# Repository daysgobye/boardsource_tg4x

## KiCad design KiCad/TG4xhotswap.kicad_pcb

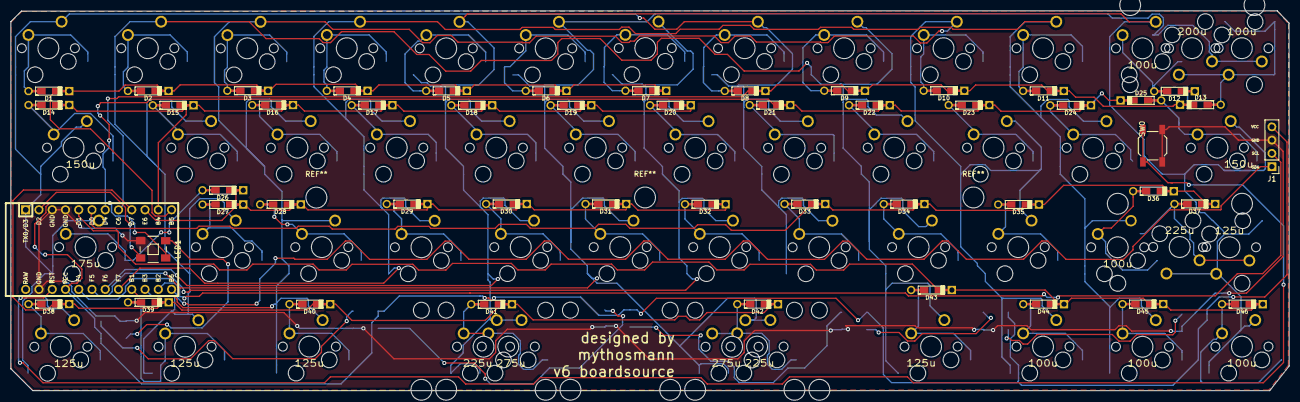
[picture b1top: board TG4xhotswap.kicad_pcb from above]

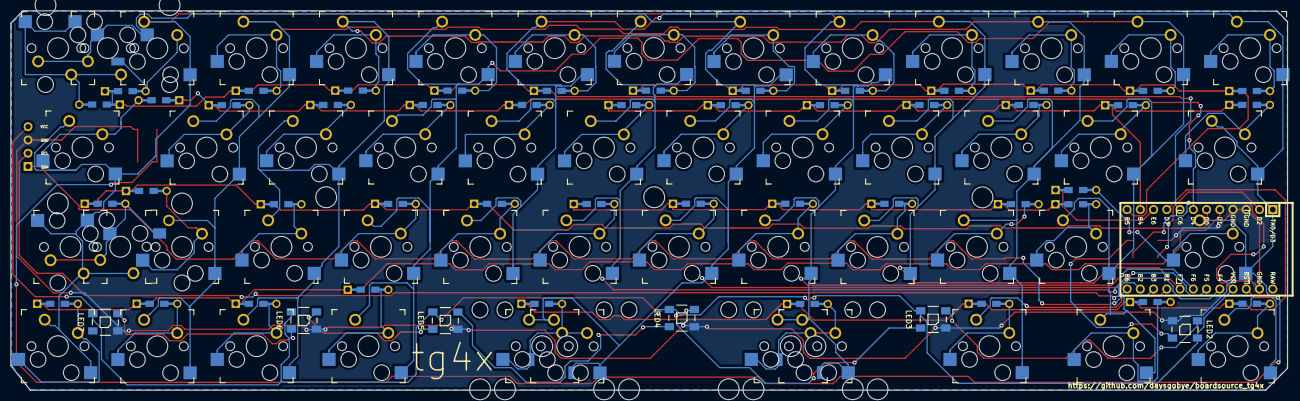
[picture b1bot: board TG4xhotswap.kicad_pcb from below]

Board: 2 copper layers, 244.8 x 72.8 mm, 106 parts (7 on the bottom side), 73 nets.

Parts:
100u, 100u#2, 100u#3, 100u#4, 100u#5, 100u#6, 125u, 125u#2, 125u#3, 125u#4, 125u#5, 150u, 150u#2, 175u, 200u, 225u, 225u#2, 225u#3, 275u, 275u#2: SW_Push; Kailh_socket_optional
D1, D2, D3, D4, D5, D6, D7, D8, D9, D10, D11, D12, D13, D14, D15, D16, D17, D18, D19, D20, D21, D22, D23, D24, D25, D26, D27, D28, D29, D30, D31, D32, D33, D34, D35, D36, D37, D38, D39, D40, D41, D42, D43, D44, D45, D46: 1N4148; Diode-dual
J1: Conn_01x04_Female; PinHeader_1x04_P2.54mm_Vertical
LED1, LED2, LED3, LED4, LED5, LED6, LED7: WS2812B
SW0: SW_Push; SW_SPST_SKQG_WithStem
SW1, SW2, SW3, SW4, SW5, SW6, SW7, SW8, SW9, SW10, SW11, SW15b1, SW16b1, SW17b1, SW18b1, SW19b1, SW20b1, SW21b1, SW22b1, SW23b1, SW24b1, SW27, SW28, SW29, SW30, SW31, SW32, SW33, SW34, SW35: SW_Push; Kailh_socket_optional
U1: ProMicro; ArduinoProMicro

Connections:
COL0: 125u.1, 150u.1, 175u.1, SW1.1, SW8.1, SW21b1.1, SW33.1, U1.1
COL1: 125u#2.1, 125u#5.1, SW2.1, SW9.1, SW15b1.1, SW22b1.1, SW27.1, SW34.1, U1.15
COL2: 100u#3.1, 125u#3.1, SW3.1, SW10.1, SW16b1.1, SW23b1.1, SW28.1, SW35.1, U1.16
COL3: 100u#2.1, 100u#4.1, SW4.1, SW11.1, SW17b1.1, SW24b1.1, SW29.1, U1.17
COL4: 100u.1, 100u#5.1, 125u#4.1, 150u#2.1, 225u#2.1, 225u#3.1, 275u#2.1, SW5.1, SW18b1.1, SW30.1, U1.18
COL5: 100u#6.2, 200u.2, 225u.1, 275u.1, SW6.1, SW19b1.1, SW31.1, U1.19
COL6: SW7.1, SW20b1.1, SW32.1, U1.20
GND: J1.3, LED1.3, LED2.3, LED3.3, LED4.3, LED5.3, LED6.3, LED7.3, SW0.2, U1.3, U1.4, U1.23
LED: LED1.4, U1.2
unnamed: D1.2, SW1.2
unnamed: D2.2, SW2.2
unnamed: D3.2, SW3.2
unnamed: D4.2, SW4.2
unnamed: D5.2, SW5.2
unnamed: D6.2, SW6.2
unnamed: D7.2, SW7.2
unnamed: D8.2, SW8.2
unnamed: D9.2, SW9.2
unnamed: D10.2, SW10.2
unnamed: D11.2, SW11.2
unnamed: 100u.2, D12.2
unnamed: 100u#6.1, 200u.1, D13.2
unnamed: 150u.2, D14.2
unnamed: D15.2, SW15b1.2
unnamed: D16.2, SW16b1.2
unnamed: D17.2, SW17b1.2
unnamed: D18.2, SW18b1.2
unnamed: D19.2, SW19b1.2
unnamed: D20.2, SW20b1.2
unnamed: D21.2, SW21b1.2
unnamed: D22.2, SW22b1.2
unnamed: D23.2, SW23b1.2
unnamed: D24.2, SW24b1.2
unnamed: 150u#2.2, D25.2
unnamed: 175u.2, D26.2
unnamed: D27.2, SW27.2
unnamed: D28.2, SW28.2
unnamed: D29.2, SW29.2
unnamed: D30.2, SW30.2
unnamed: D31.2, SW31.2
unnamed: D32.2, SW32.2
unnamed: D33.2, SW33.2
unnamed: D34.2, SW34.2
unnamed: D35.2, SW35.2
unnamed: 100u#2.2, D36.2
unnamed: 125u#4.2, 225u#3.2, D37.2
unnamed: 125u.2, D38.2
unnamed: 125u#2.2, D39.2
unnamed: 125u#3.2, D40.2
unnamed: 225u#2.2, 275u#2.2, D41.2
unnamed: 225u.2, 275u.2, D42.2
unnamed: 125u#5.2, D43.2
unnamed: 100u#3.2, D44.2
unnamed: 100u#4.2, D45.2
unnamed: 100u#5.2, D46.2
unnamed: LED1.2, LED2.4
unnamed: LED2.2, LED3.4
unnamed: LED3.2, LED4.4
unnamed: LED4.2, LED5.4
unnamed: LED5.2, LED6.4
unnamed: LED6.2, LED7.4
ROW0: D1.1, D2.1, D3.1, D4.1, D5.1, D6.1, D7.1, U1.12
ROW1: D14.1, D15.1, D16.1, D17.1, D18.1, D19.1, D20.1, U1.11
ROW2: D26.1, D27.1, D28.1, D29.1, D30.1, D31.1, D32.1, U1.10
ROW3: D38.1, D39.1, D40.1, D41.1, D42.1, U1.9
ROW4: D8.1, D9.1, D10.1, D11.1, D12.1, D13.1, U1.8
ROW5: D21.1, D22.1, D23.1, D24.1, D25.1, U1.7
ROW6: D33.1, D34.1, D35.1, D36.1, D37.1, U1.6
ROW7: D43.1, D44.1, D45.1, D46.1, U1.5
RST: SW0.1, U1.22
SCL: J1.2, U1.14
SDA: J1.1, U1.13
VCC: J1.4, LED1.1, LED2.1, LED3.1, LED4.1, LED5.1, LED6.1, LED7.1, U1.21

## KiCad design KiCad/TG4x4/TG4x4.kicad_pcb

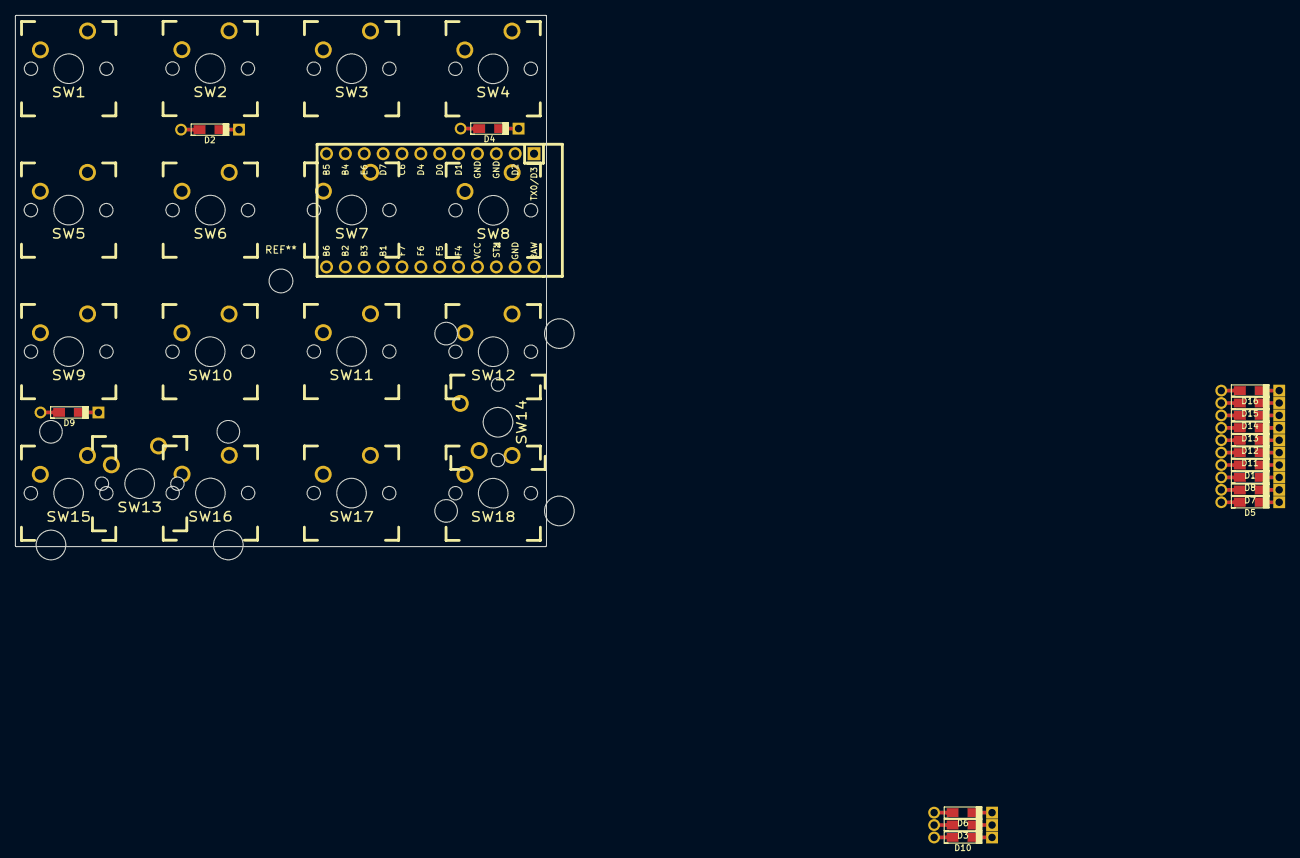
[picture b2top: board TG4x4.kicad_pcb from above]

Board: 2 copper layers, 71.5 x 71.5 mm, 35 parts (0 on the bottom side), 25 nets, no tracks yet.

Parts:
D1, D2, D3, D4, D5, D6, D7, D8, D9, D10, D11, D12, D13, D14, D15, D16: D; Diode-dual
SW1, SW2, SW3, SW4, SW5, SW6, SW7, SW8, SW9, SW10, SW11, SW12, SW15, SW16, SW17, SW18: SW_Push; MX_PCB_100H
SW13: SW_Push; MX_PCB_200H
SW14: SW_Push; MX_PCB_200V
U1: ProMicro; ArduinoProMicro

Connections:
/COL0: SW1.2, SW5.2, SW9.2, SW13.2, SW15.2, U1.1
/COL1: SW2.2, SW6.2, SW10.2, SW16.2, U1.7
/COL2: SW3.2, SW7.2, SW11.2, SW17.2, U1.8
/COL3: SW4.2, SW8.2, SW12.2, SW14.2, SW18.2, U1.9
/ROW0: D1.1, D2.1, D3.1, D4.1, U1.20
/ROW1: D5.1, D6.1, D7.1, D8.1, U1.19
/ROW2: D9.1, D10.1, D11.1, D12.1, U1.18
/ROW3: D13.1, D14.1, D15.1, D16.1, U1.17
GND: U1.3, U1.4, U1.23
unnamed: D1.2, SW1.1
unnamed: D2.2, SW2.1
unnamed: D3.2, SW3.1
unnamed: D4.2, SW4.1
unnamed: D5.2, SW5.1
unnamed: D6.2, SW6.1
unnamed: D7.2, SW7.1
unnamed: D8.2, SW8.1
unnamed: D9.2, SW9.1
unnamed: D10.2, SW10.1
unnamed: D11.2, SW11.1
unnamed: D12.2, SW12.1
unnamed: D13.2, SW13.1, SW15.1
unnamed: D14.2, SW16.1
unnamed: D15.2, SW17.1
unnamed: D16.2, SW14.1, SW18.1

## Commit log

2020-06-14 added the hotswap tg4x
